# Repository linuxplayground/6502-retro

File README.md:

# 6502-Retro!

Inspired by the Z80-Retro! see: [https://github.com/z80-retro](https://github.com/z80-retro)
I decided to see if I could put together a small 6502 based project with a similar
design philosphy.  The main goals of the project are:

1. The base board must be no larger than 100mm x 100mm to leverage the cheaper
    manufacturing options.
2. The base board must provide all required functionality to be minimially operational.
3. Daughter boards will provide additional peripherals such as Graphics and Audio

## Base Board

You can find the hardware 
[schematic](./hardware/6502-retro/6502-retro.pdf) and gerber files for the base 
board in [hardware/6502-retro](./hardware/6502-retro/).

## Expansion Boards

This project contains two expansion boards.

### NOTE !!

One of the expansion slots (J1) is too close to the BAUD RATE Oscilator on the 
base board.  It can be used for manual jumper wires maybe, but I would not risk
putting a card in there as the solder joints on the back of the card will short
against the metal oscilator can for the baud rate clock.

### F18A (TMS9918A FPGA)

The F18A from [dnotq](https://dnotq.io/f18a/intro.html) is mounted with some
glue logic on an expansion board.  It provides all the same features as the 
TMS9918A VDP along with some additional enhancments that can be accessed in
software.

You can find the hardware [schematic here.](./hardware/6502-retro-f18a/6502-retro-f18a.pdf)

### General Purpose IO + PS/2

You can find the hardware [schematic here.](./hardware/6502-retro-io/6502-retro-io.pdf)

Note: PS/2 Support is designed for the [PERIBOARD-409 P - Mini PS/2 keyboard](https://perixx.com/products/ps2-mini-keyboard)

This board has a "sign-on" routine that's handled in the PIC16F628A
microcontroller.  The code for the MCU is included [here](./pic16f628a/)

The more generic / standard PS/2 Keyboards will require the MCU code to be
altered.

## Memory Map

The memory map is given by an AT22v10Q PLD which provides ranges in the table below.  These values are also defined in [6502-retro-rom.cfg](./software/6502-retro-rom.cfg)

|Range     |Description     |Size   | Decoder Pins| Comments
|---       |---             |---    |---          |---
|0000-00FF |Zero Page       |0x100  |             |
|0100-0200 |Stack           |0x100  |             |
|0200-0FFF |SYSRAM          |0xE00  |             |
|1000-7EFF |RAM             |0x6F00 |             |
|          |                |       |             |
|7F00-7F10 |UNMAPPED        |0x16   |             |
|7F10-7F1F |FREE            |0x16   | IOCS1 + A4  | IOCS1 is clock qualified
|7F20-7F2F |ACIA            |0x16   | IOCS1 + A5  |
|7F30-7F3F |UNMAPPED        |0x16   |             |
|7F40-7F4F |F18A / TMS9918A |0x16   | IOCS1 + A6  |
|7F50-7F8F |UNAMPPED        |0x64   |             |
|7F90-7F90 |VIA             |0x16   | IOCS2 + A4  | IOCS2 is not clock qualified
|7FA0-7FAF |FREE            |0x16   | IOCS2 + A5  |
|7FB0-7FBF |UMAPPED         |0x16   |             | 
|7FC0-7FCF |FREE            |0x16   | IOCS2 + A6  |
|7FD0-7FEF |UNMAPPED        |0x64   |             |

* IOCS1 is only active when phi2 is HIGH in the shown address ranges.
* IOCS2 is active in the shown address ranges without any influence by phi2.

See the [PLD Code](./pld/6502-RETRO-PLD.PLD) for the WinCUPL design file.

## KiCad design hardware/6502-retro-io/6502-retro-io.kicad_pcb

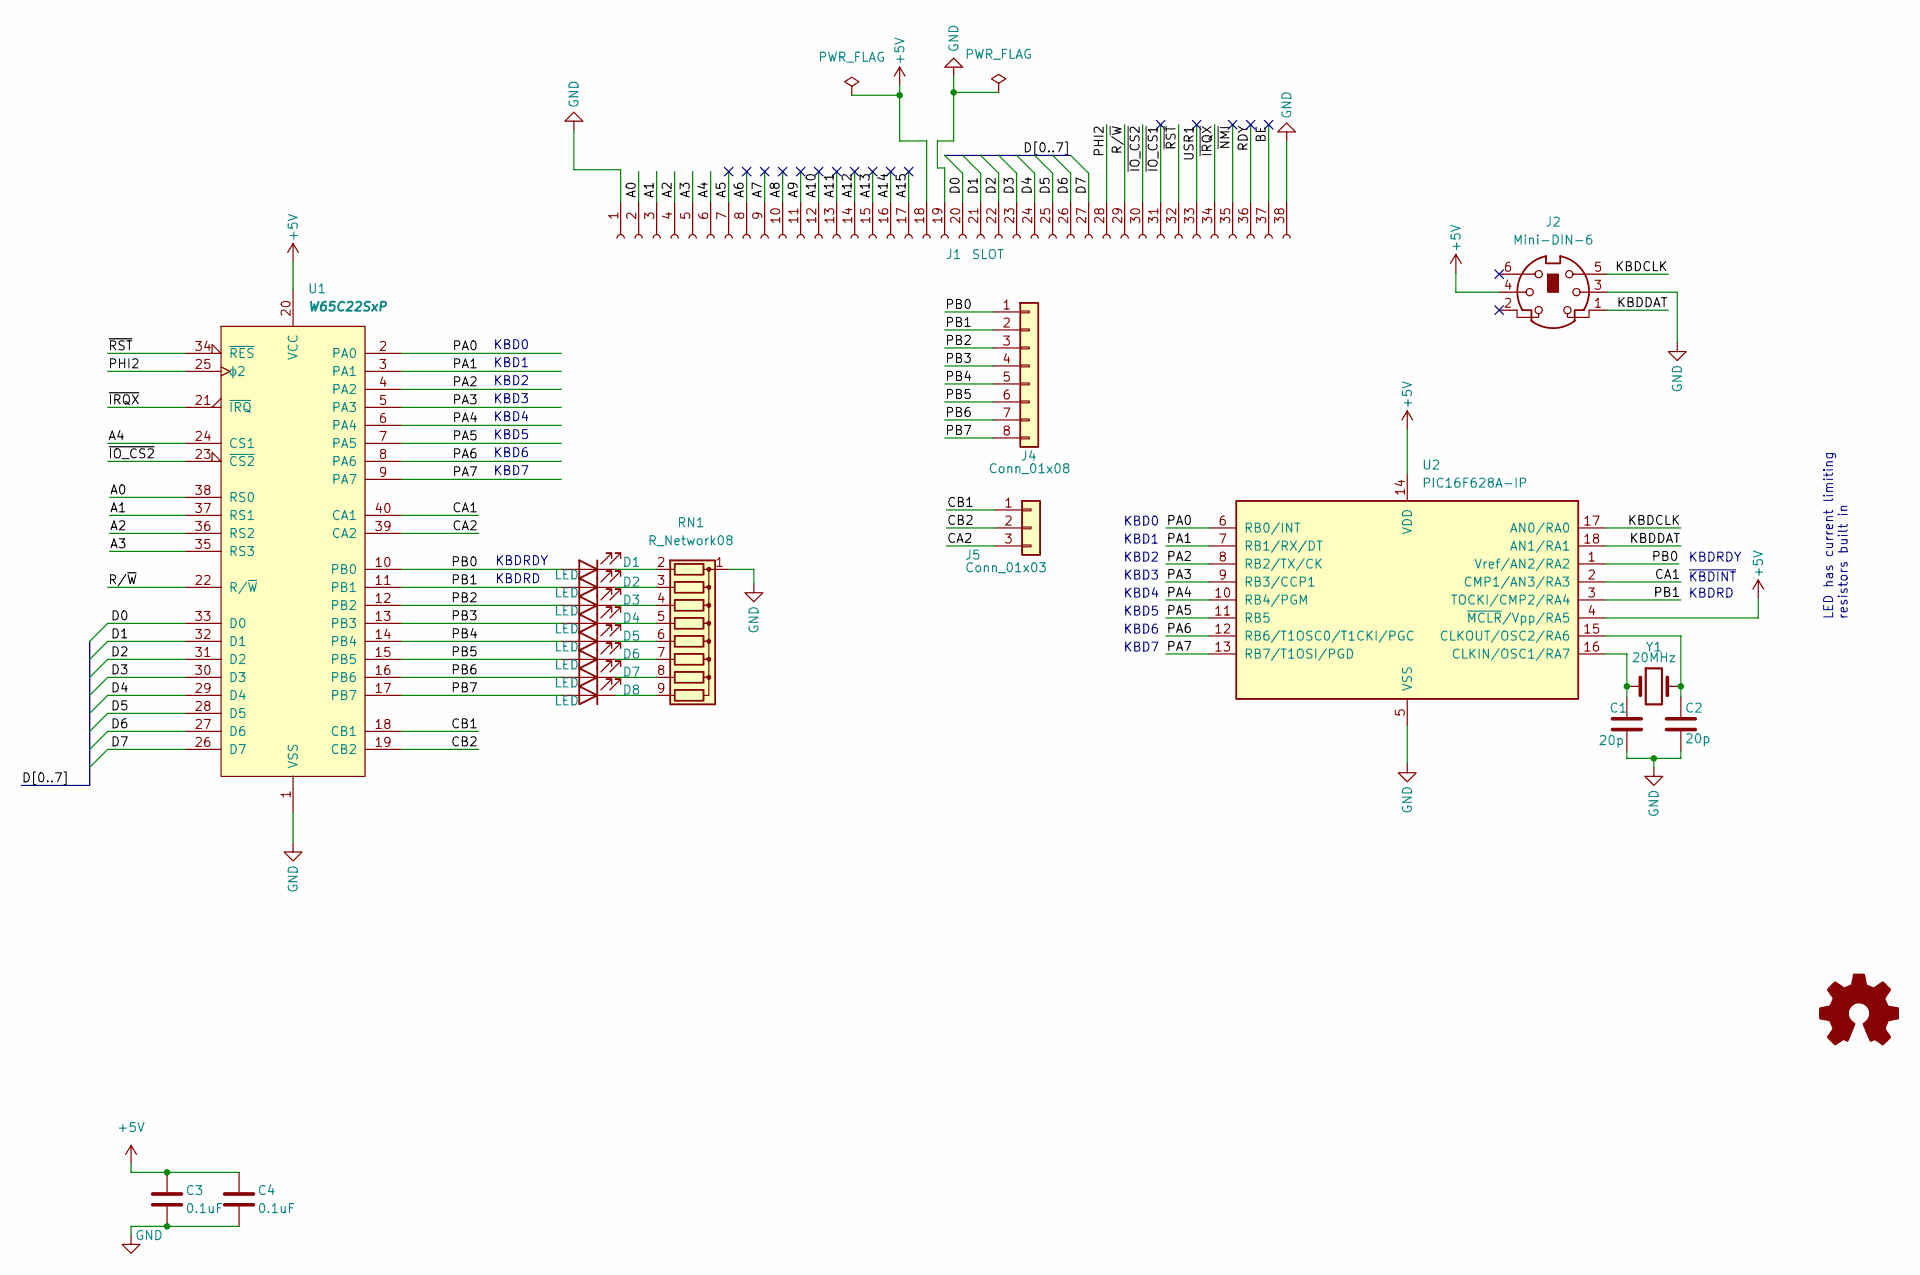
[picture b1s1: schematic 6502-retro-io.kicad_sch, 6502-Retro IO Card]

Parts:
C1, C2: 20p; C_Disc_D3.0mm_W2.0mm_P2.50mm
C3, C4: 0.1uF; C_Disc_D3.0mm_W2.0mm_P2.50mm
D1, D2, D3, D4, D5, D6, D7, D8: LED; LED_D5.0mm
J1: SLOT; PinHeader_1x38_P2.54mm_Horizontal
J2: Mini-DIN-6; Connector_Mini-DIN_Female_6Pin_2rows
J4: Conn_01x08; PinHeader_1x08_P2.54mm_Horizontal
J5: Conn_01x03; PinHeader_1x03_P2.54mm_Horizontal
RN1: R_Network08; R_Array_SIP9
U1: W65C22SxP; DIP-40_W15.24mm_Socket
U2: PIC16F628A-IP; DIP-18_W7.62mm_Socket
Y1: 20MHz; Crystal_HC18-U_Vertical

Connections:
+5V: C3.1, C4.1, J1.18, J2.4, U1.20 (VCC), U2.4 (~MCLR/Vpp/RA5), U2.14 (VDD)
/A0: J1.2, U1.38 (RS0)
/A1: J1.3, U1.37 (RS1)
/A2: J1.4, U1.36 (RS2)
/A3: J1.5, U1.35 (RS3)
/A4: J1.6, U1.24 (CS1)
/A5: J1.7
/A6: J1.8
/A7: J1.9
/A8: J1.10
/A9: J1.11
/A10: J1.12
/A11: J1.13
/A12: J1.14
/A13: J1.15
/A14: J1.16
/A15: J1.17
/BE: J1.37
/CA1: U1.40 (CA1), U2.2 (CMP1/AN3/RA3)
/CA2: J5.3, U1.39 (CA2)
/CB1: J5.1, U1.18 (CB1)
/CB2: J5.2, U1.19 (CB2)
/D0: J1.20, U1.33 (D0)
/D1: J1.21, U1.32 (D1)
/D2: J1.22, U1.31 (D2)
/D3: J1.23, U1.30 (D3)
/D4: J1.24, U1.29 (D4)
/D5: J1.25, U1.28 (D5)
/D6: J1.26, U1.27 (D6)
/D7: J1.27, U1.26 (D7)
/KBDCLK: J2.5, U2.17 (AN0/RA0)
/KBDDAT: J2.1, U2.18 (AN1/RA1)
/PA0: U1.2 (PA0), U2.6 (RB0/INT)
/PA1: U1.3 (PA1), U2.7 (RB1/RX/DT)
/PA2: U1.4 (PA2), U2.8 (RB2/TX/CK)
/PA3: U1.5 (PA3), U2.9 (RB3/CCP1)
/PA4: U1.6 (PA4), U2.10 (RB4/PGM)
/PA5: U1.7 (PA5), U2.11 (RB5)
/PA6: U1.8 (PA6), U2.12 (RB6/T1OSC0/T1CKI/PGC)
/PA7: U1.9 (PA7), U2.13 (RB7/T1OSI/PGD)
/PB0: D1.2 (A), J4.1, U1.10 (PB0), U2.1 (Vref/AN2/RA2)
/PB1: D2.2 (A), J4.2, U1.11 (PB1), U2.3 (TOCKI/CMP2/RA4)
/PB2: D3.2 (A), J4.3, U1.12 (PB2)
/PB3: D4.2 (A), J4.4, U1.13 (PB3)
/PB4: D5.2 (A), J4.5, U1.14 (PB4)
/PB5: D6.2 (A), J4.6, U1.15 (PB5)
/PB6: D7.2 (A), J4.7, U1.16 (PB6)
/PB7: D8.2 (A), J4.8, U1.17 (PB7)
/PHI2: J1.28, U1.25 (ϕ2)
/RDY: J1.36
/R/~W: J1.29, U1.22 (R/~W)
/USR1: J1.33
/~IO_CS1: J1.31
/~IO_CS2: J1.30, U1.23 (~CS2)
/~IRQX: J1.34, U1.21 (~IRQ)
/~NMI: J1.35
/~RST: J1.32, U1.34 (~RES)
GND: C1.2, C2.2, C3.2, C4.2, J1.1, J1.19, J1.38, J2.3, RN1.1 (common), U1.1 (VSS), U2.5 (VSS)
unnamed: C1.1, U2.16 (CLKIN/OSC1/RA7), Y1.1
unnamed: C2.1, U2.15 (CLKOUT/OSC2/RA6), Y1.2
unnamed: D1.1 (K), RN1.2 (R1)
unnamed: D2.1 (K), RN1.3 (R2)
unnamed: D3.1 (K), RN1.4 (R3)
unnamed: D4.1 (K), RN1.5 (R4)
unnamed: D5.1 (K), RN1.6 (R5)
unnamed: D6.1 (K), RN1.7 (R6)
unnamed: D7.1 (K), RN1.8 (R7)
unnamed: D8.1 (K), RN1.9 (R8)

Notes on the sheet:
KBD6
KBD2
KBD4
KBD0
~{KBDINT}
KBDRDY
KBD7
KBD1
KBDRD
KBD3
KBD5
LED has current limiting resistors built in

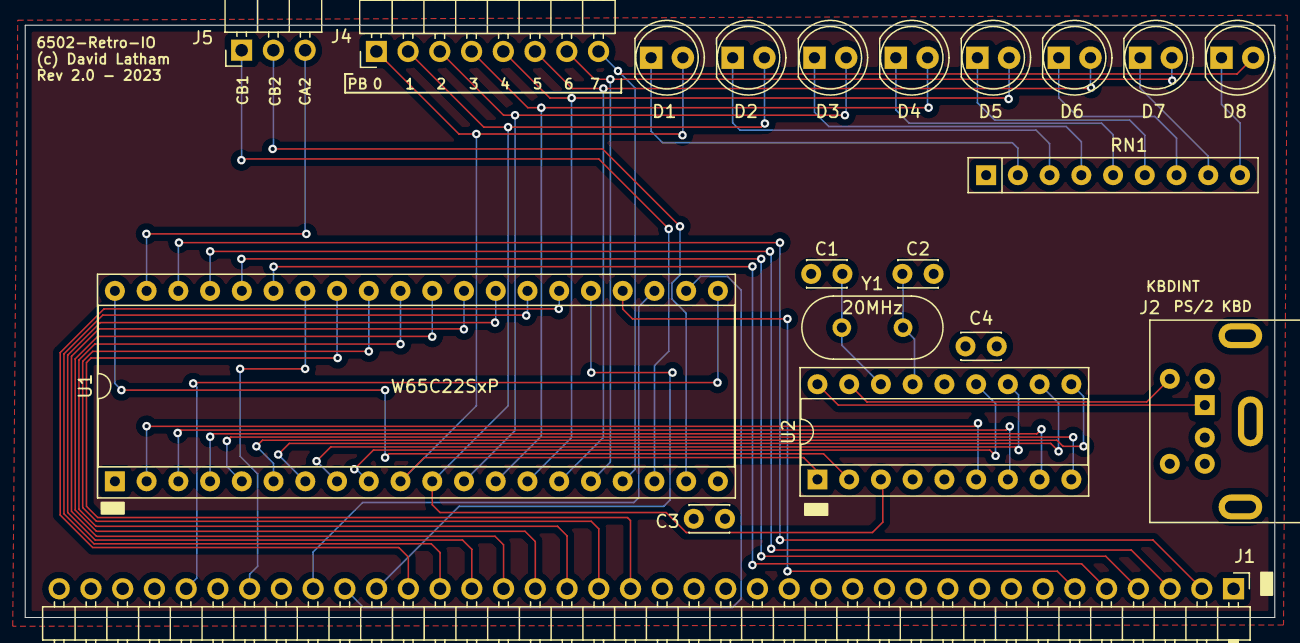
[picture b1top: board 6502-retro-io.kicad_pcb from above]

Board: 4 copper layers, 100.0 x 47.4 mm, 20 parts (0 on the bottom side), 52 nets.

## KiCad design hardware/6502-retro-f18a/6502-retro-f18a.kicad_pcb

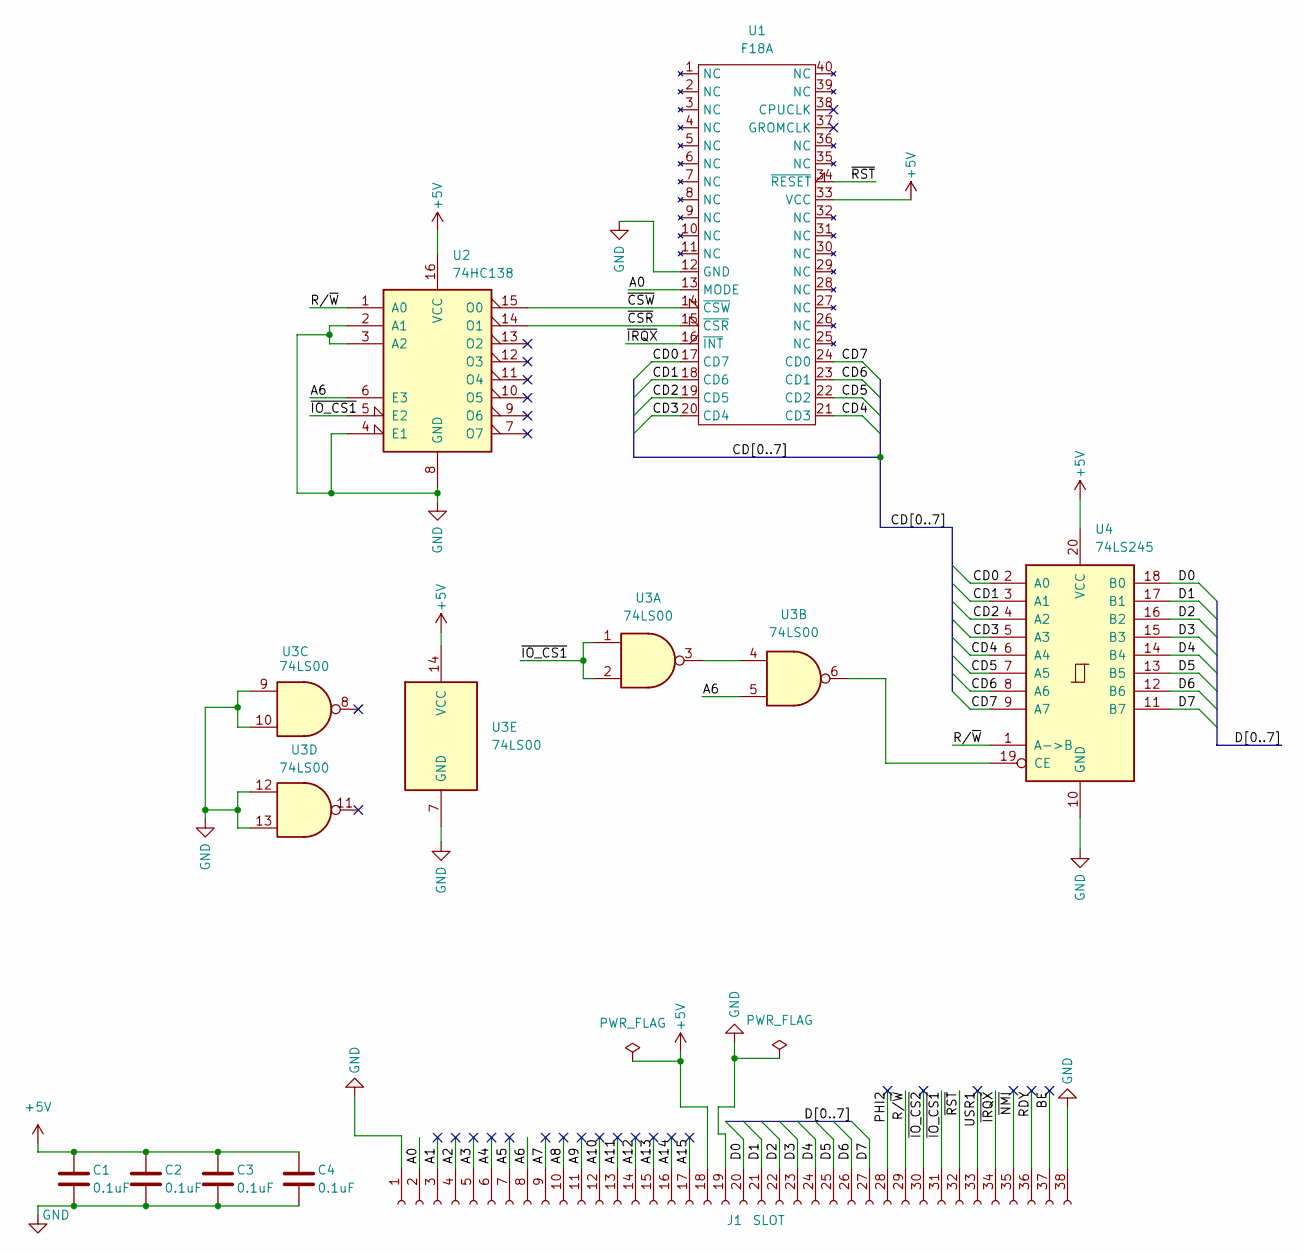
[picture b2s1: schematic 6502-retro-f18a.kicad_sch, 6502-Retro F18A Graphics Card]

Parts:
C1, C2, C3, C4: 0.1uF; C_Disc_D3.0mm_W2.0mm_P2.50mm
J1: SLOT; PinHeader_1x38_P2.54mm_Horizontal
U1: F18A; DIP-40_W15.24mm_Socket
U2: 74HC138; DIP-16_W7.62mm_Socket
U3: 74LS00
U4: 74LS245; DIP-20_W7.62mm_Socket

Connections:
+5V: C1.1, C2.1, C3.1, C4.1, J1.18, U1.33 (VCC), U2.16 (VCC), U3.14 (VCC), U4.20 (VCC)
/A0: J1.2, U1.13 (MODE)
/A1: J1.3
/A2: J1.4
/A3: J1.5
/A4: J1.6
/A5: J1.7
/A6: J1.8, U2.6 (E3), U3.5
/A7: J1.9
/A8: J1.10
/A9: J1.11
/A10: J1.12
/A11: J1.13
/A12: J1.14
/A13: J1.15
/A14: J1.16
/A15: J1.17
/BE: J1.37
/CD0: U1.17 (CD7), U4.2 (A0)
/CD1: U1.18 (CD6), U4.3 (A1)
/CD2: U1.19 (CD5), U4.4 (A2)
/CD3: U1.20 (CD4), U4.5 (A3)
/CD4: U1.21 (CD3), U4.6 (A4)
/CD5: U1.22 (CD2), U4.7 (A5)
/CD6: U1.23 (CD1), U4.8 (A6)
/CD7: U1.24 (CD0), U4.9 (A7)
/D0: J1.20, U4.18 (B0)
/D1: J1.21, U4.17 (B1)
/D2: J1.22, U4.16 (B2)
/D3: J1.23, U4.15 (B3)
/D4: J1.24, U4.14 (B4)
/D5: J1.25, U4.13 (B5)
/D6: J1.26, U4.12 (B6)
/D7: J1.27, U4.11 (B7)
/PHI2: J1.28
/RDY: J1.36
/R/~W: J1.29, U2.1 (A0), U4.1 (A->B)
/USR1: J1.33
/~CSR: U1.15 (~CSR), U2.14 (O1)
/~CSW: U1.14 (~CSW), U2.15 (O0)
/~IO_CS1: J1.31, U2.5 (E2), U3.1, U3.2
/~IO_CS2: J1.30
/~IRQX: J1.34, U1.16 (~INT)
/~NMI: J1.35
/~RST: J1.32, U1.34 (~RESET)
unnamed: U3.3, U3.4
unnamed: U3.6, U4.19 (CE)

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
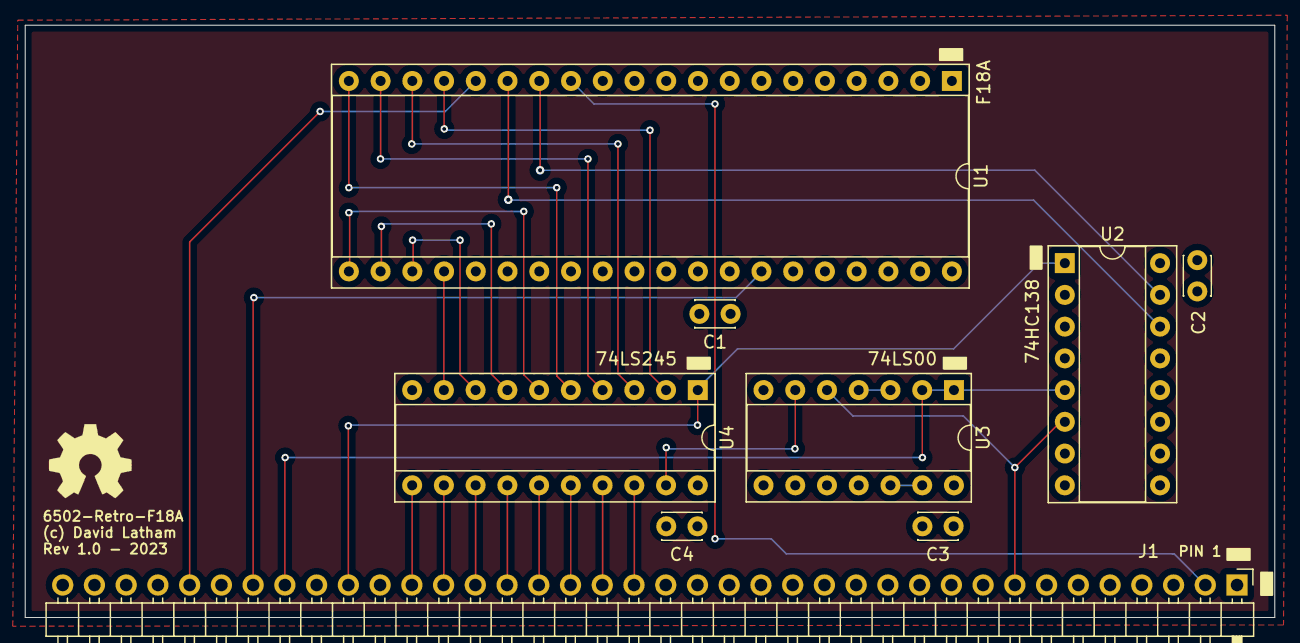
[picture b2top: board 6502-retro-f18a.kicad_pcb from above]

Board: 4 copper layers, 100.0 x 47.4 mm, 9 parts (0 on the bottom side), 28 nets.

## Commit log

2023-07-08 initial import
2023-07-09 progress on rom examples
2023-07-12 remove old hardware
2023-07-18 refresh from be6502
2023-07-18 clean up loadables etc.
2023-07-21 working-os without VDP or Audio
2023-07-24 OS will replace software
2023-07-25 Add examples
2023-07-25 updated hardware
2023-07-25 removed software directory
2023-07-25 rename os to software
2023-07-26 add pic16f628a
2023-07-26 basic examples
2023-07-28 basic snake game is working - no-apples
2023-07-29 clear screen with spaces not nulls
2023-07-29 add gitignore
2023-07-29 chunky font from nabu-games
2023-07-30 Snake is playable now.
2023-07-30 comments
2023-07-31 add c software
2023-07-31 CLS now goes home
2023-07-31 Add C code
2023-08-08 More mature OS with more mature C support. Snake in C!
2023-08-08 update to readme - warning about J1 slot location
2023-08-09 we dont need to terminate sprintf strings ourselves.
2023-08-09 remove c
2023-08-09 clean up
2023-08-09 add gitignores
2023-08-15 CTRL+C, blinky, and keybard basic
